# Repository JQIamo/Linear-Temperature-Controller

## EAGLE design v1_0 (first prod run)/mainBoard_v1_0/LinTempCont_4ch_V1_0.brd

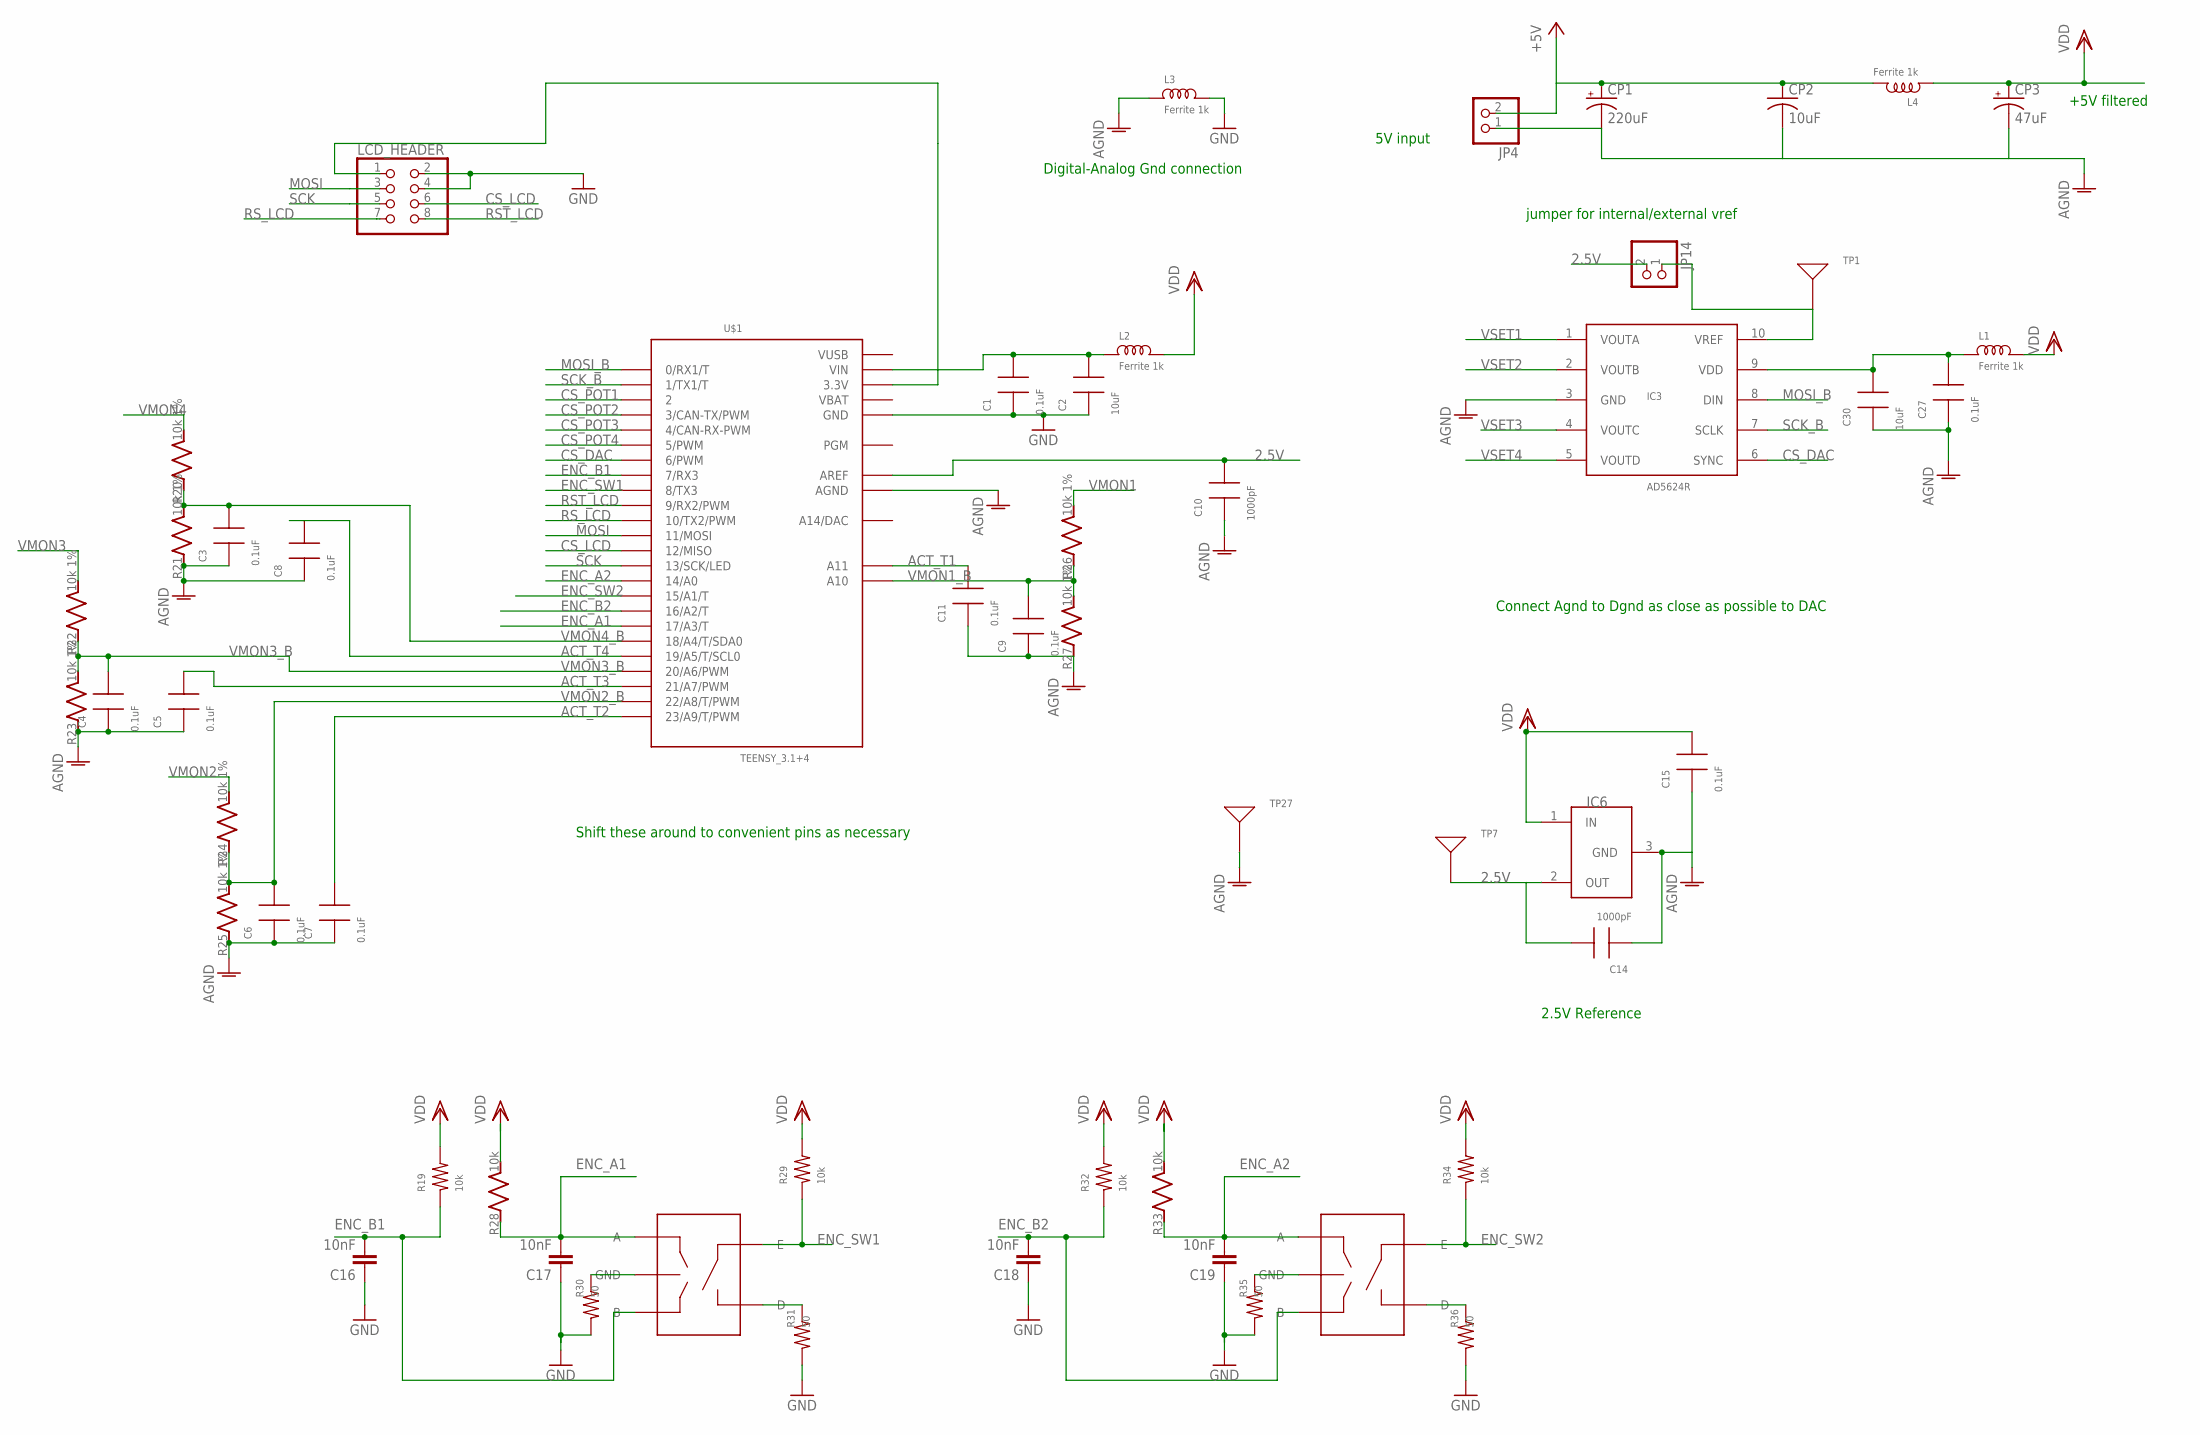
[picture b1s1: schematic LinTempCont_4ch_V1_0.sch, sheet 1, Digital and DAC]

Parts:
C1, C3, C4, C5, C6, C7, C8, C9, C11, C15, C27: 0.1uF; 0603
C2, C30: 10uF; 0805
C10, C14: 1000pF; 0603
C16, C17, C18, C19: 10nF; C0603
CP1: 220uF; PANASONIC_F
CP2: 10uF; C0805K
CP3: 47uF; CT7343
ENC1, ENC2: PEC09; PEC092320FS
IC3: AD5624R; MSOP10
IC6: TS6001; SOT-23
JP4: SCRWTRM-1X2; 1X02_SCRWTRM
JP14: PINHD-1X2; 1X02
L1, L2, L3, L4: Ferrite 1k; 0805
LCD_HEADER: PINHD-2X4-SHROUD; ML08
R19, R29, R32, R34: 10k; 0603
R20, R21, R22, R23, R24, R25, R26, R27: 10k 1%; R_0603
R28, R33: 10k; R_0603
R30, R31, R35, R36: 50; 0603
TP1, TP7, TP27: TESTPT; 1206TESTPAD
U$1: TEENSY_3.1+4

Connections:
2.5V: C10.2, C14.2, IC6.2 (OUT), JP14.2, TP7.P$1, U$1.AREF; also elsewhere on the board
3.3V: LCD_HEADER.1, U$1.3.3V, U$1.3.3V1 (3.3V)
+5V: CP1.+, CP2.1, JP4.2, L4.2
ACT_T1: C11.2, U$1.A11; also elsewhere on the board
ACT_T2: C7.2, U$1.23/A9 (23/A9/T/PWM); also elsewhere on the board
ACT_T3: C5.2, U$1.21/A7 (21/A7/PWM); also elsewhere on the board
ACT_T4: C8.2, U$1.19/A5 (19/A5/T/SCL0); also elsewhere on the board
AGND: C3.1, C4.1, C5.1, C6.1, C7.1, C8.1, C9.1, C10.1, C11.1, C14.1, C15.1, C27.1, C30.1, CP1.-, CP2.2, CP3.-, IC3.3 (GND), IC6.3 (GND), JP4.1, L3.1, R21.P$1 (1), R23.P$1 (1), R25.P$1 (1), R27.P$1 (1), TP27.P$1, U$1.AGND; also elsewhere on the board
CS_DAC: IC3.6 (SYNC), U$1.6 (6/PWM)
CS_LCD: LCD_HEADER.6, U$1.12 (12/MISO)
CS_POT1: U$1.2; also elsewhere on the board
CS_POT2: U$1.3 (3/CAN-TX/PWM); also elsewhere on the board
CS_POT3: U$1.4 (4/CAN-RX-PWM); also elsewhere on the board
CS_POT4: U$1.5 (5/PWM); also elsewhere on the board
DGND: C1.1, C2.1, C16.1, C17.1, C18.1, C19.1, L3.2, LCD_HEADER.2, LCD_HEADER.4, R30.1, R31.1, R35.1, R36.1, U$1.GND, U$1.GND1 (GND); also elsewhere on the board
ENC_A1: C17.2, ENC1.A, R28.P$1 (1), U$1.17/A3 (17/A3/T)
ENC_A2: C19.2, ENC2.A, R33.P$1 (1), U$1.14/A0
ENC_B1: C16.2, ENC1.B, R19.1, U$1.7 (7/RX3)
ENC_B2: C18.2, ENC2.B, R32.1, U$1.16/A2 (16/A2/T)
ENC_SW1: ENC1.E, R29.1, U$1.8 (8/TX3)
ENC_SW2: ENC2.E, R34.1, U$1.15/A1 (15/A1/T)
MOSI: LCD_HEADER.3, U$1.11 (11/MOSI)
MOSI_B: IC3.8 (DIN), U$1.0 (0/RX1/T); also elsewhere on the board
unnamed: IC3.10 (VREF), JP14.1, TP1.P$1
unnamed: ENC1.C (GND), R30.2
unnamed: ENC1.D, R31.2
unnamed: ENC2.C (GND), R35.2
unnamed: ENC2.D, R36.2
unnamed: C27.2, C30.2, IC3.9 (VDD), L1.1
unnamed: C1.2, C2.2, L2.1, U$1.VIN
RST_LCD: LCD_HEADER.8, U$1.9 (9/RX2/PWM)
RS_LCD: LCD_HEADER.7, U$1.10 (10/TX2/PWM)
SCK: LCD_HEADER.5, U$1.13 (13/SCK/LED)
SCK_B: IC3.7 (SCLK), U$1.1 (1/TX1/T); also elsewhere on the board
VBAT: U$1.VBAT
VDD: C15.2, CP3.+, IC6.1 (IN), L1.2, L2.2, L4.1, R19.2, R28.P$2 (2), R29.2, R32.2, R33.P$2 (2), R34.2; also elsewhere on the board
VMON1: R26.P$2 (2); also elsewhere on the board
VMON1_B: C9.2, R26.P$1 (1), R27.P$2 (2), U$1.A10
VMON2: R24.P$2 (2); also elsewhere on the board
VMON2_B: C6.2, R24.P$1 (1), R25.P$2 (2), U$1.22/A8 (22/A8/T/PWM)
VMON3: R22.P$2 (2); also elsewhere on the board
VMON3_B: C4.2, R22.P$1 (1), R23.P$2 (2), U$1.20/A6 (20/A6/PWM)
VMON4: R20.P$2 (2); also elsewhere on the board
VMON4_B: C3.2, R20.P$1 (1), R21.P$2 (2), U$1.18/A4 (18/A4/T/SDA0)
VSET1: IC3.1 (VOUTA); also elsewhere on the board
VSET2: IC3.2 (VOUTB); also elsewhere on the board
VSET3: IC3.4 (VOUTC); also elsewhere on the board
VSET4: IC3.5 (VOUTD); also elsewhere on the board
VUSB: U$1.VUSB

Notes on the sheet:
Shift these around to convenient pins as necessary
Digital-Analog Gnd connection
Connect Agnd to Dgnd as close as possible to DAC
2.5V Reference
+5V filtered
5V input
jumper for internal/external vref

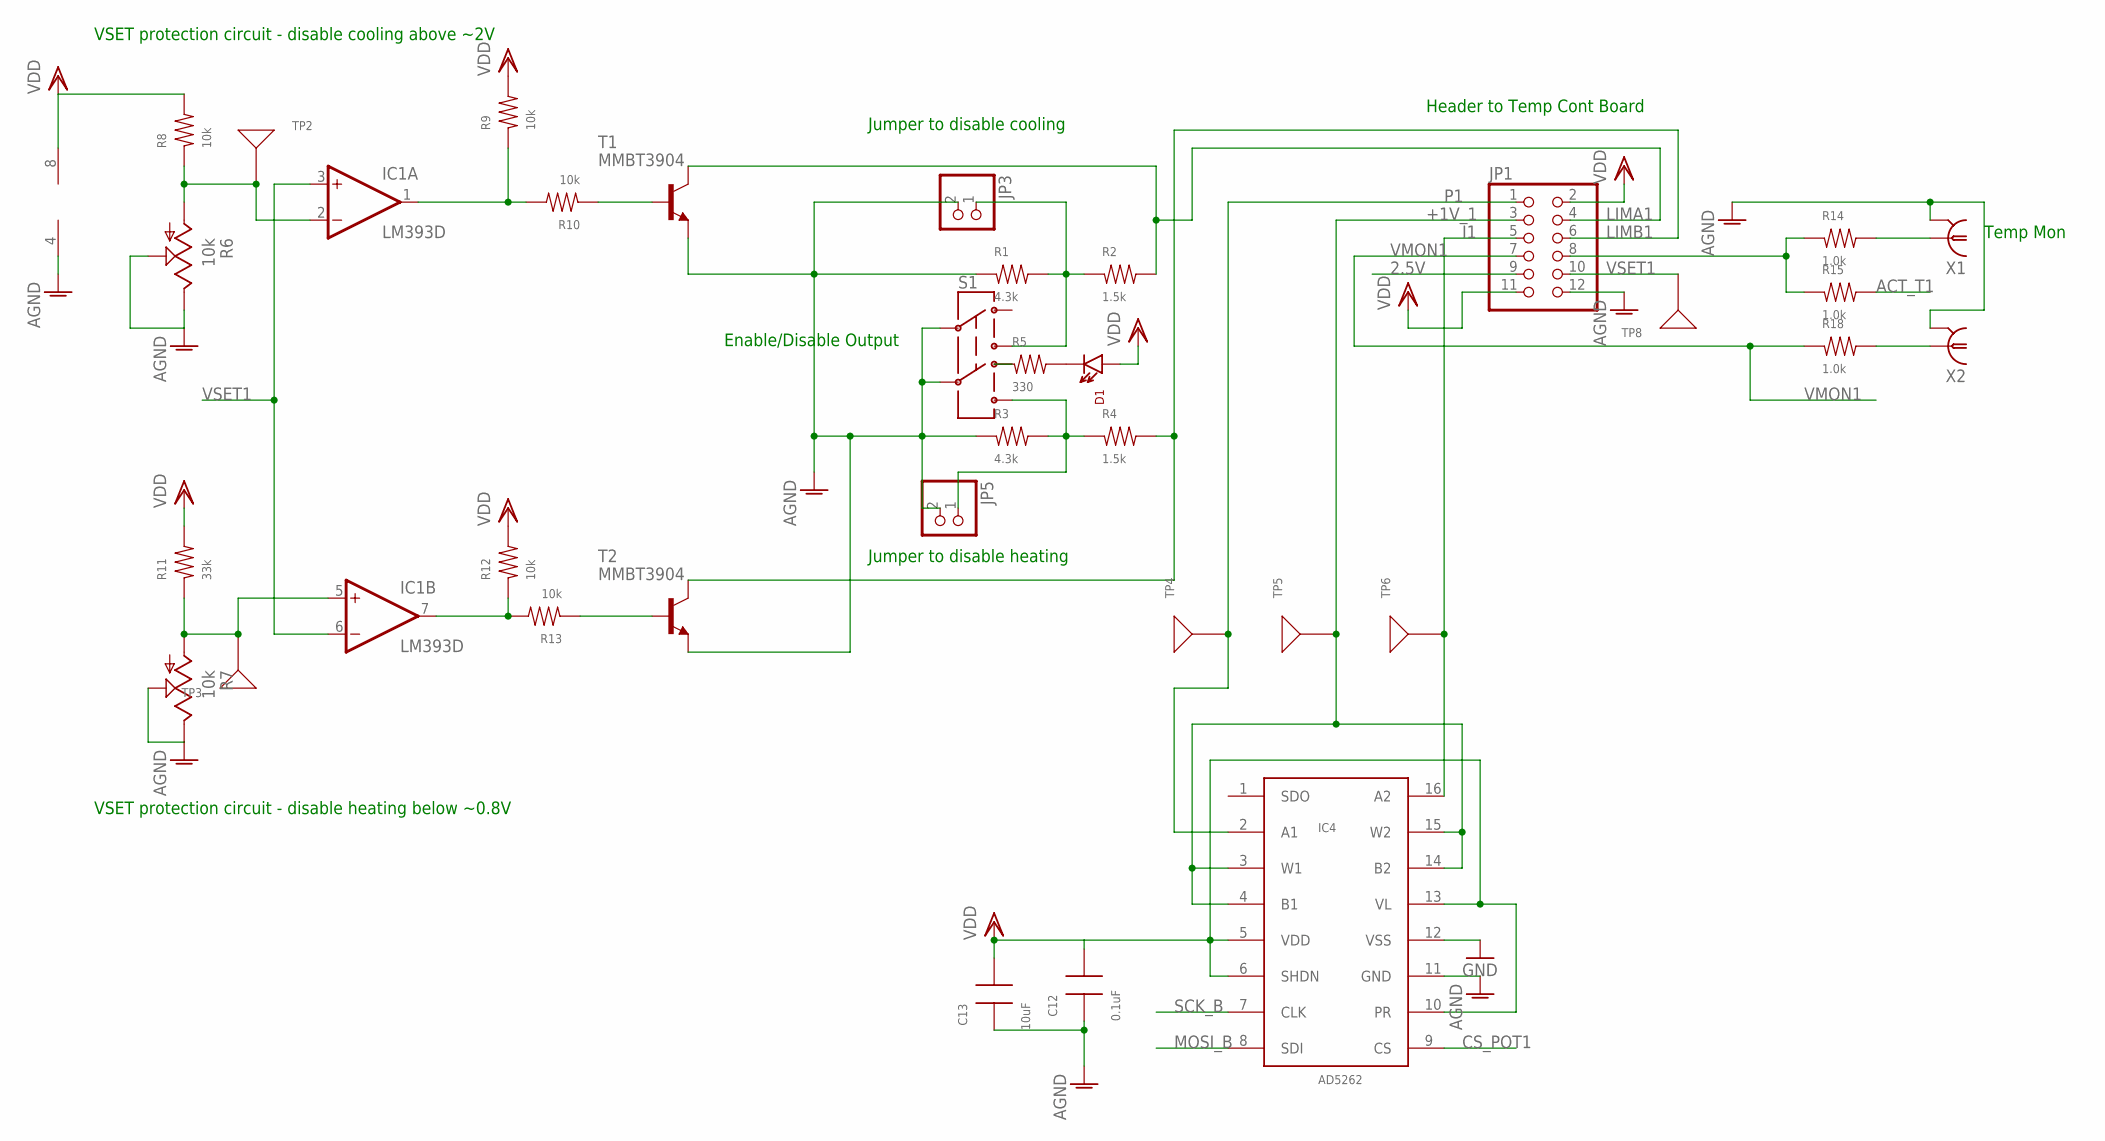
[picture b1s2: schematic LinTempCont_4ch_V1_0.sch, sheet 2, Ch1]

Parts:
C12: 0.1uF; 0603
C13: 10uF; 0805
D1: LED/MINI-IND; HLMP--F0010
IC1: LM393D; SO08
IC4: AD5262; TSSOP16
JP1: PINHD-2X6/90; 2X06/90
JP3, JP5: PINHD-1X2; 1X02
R1, R3: 4.3k; 0603
R2, R4: 1.5k; 0603
R5: 330; 0603
R6, R7: 10k; 64WPOT
R8, R9, R10, R12, R13: 10k; 0603
R11: 33k; 0603
R14, R15, R18: 1.0k; 0603
S1: SWITCH-DPDT/VER; E-SWITCH-100-M7
T1, T2: MMBT3904; SOT-23
TP2, TP3, TP4, TP5, TP6, TP8: TESTPT; 1206TESTPAD
X1, X2: BNC-H; BNC90

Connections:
2.5V: JP1.9; also elsewhere on the board
+1V_1: IC4.3 (W1), IC4.4 (B1), IC4.14 (B2), IC4.15 (W2), JP1.3, TP5.P$1
ACT_T1: R15.2; also elsewhere on the board
AGND: C12.1, C13.1, IC1.4 (V-), IC4.11 (GND), JP1.12, JP3.2, JP5.2, R1.1, R3.1, R6.P$2 (2), R6.P$3 (3), R7.P$2 (2), R7.P$3 (3), S1.P$2 (2), S1.P$5 (5), T1.2 (E), T2.2 (E), X1.2, X2.2; also elsewhere on the board
CS_POT1: IC4.9 (CS); also elsewhere on the board
DGND: IC4.12 (VSS); also elsewhere on the board
I1: IC4.16 (A2), JP1.5, TP6.P$1
LIMA1: JP1.4, R2.2, T1.3 (C)
LIMB1: JP1.6, R4.2, T2.3 (C)
MOSI_B: IC4.8 (SDI); also elsewhere on the board
unnamed: JP3.1, R1.2, R2.1, S1.P$3 (3)
unnamed: R14.2, X1.1
unnamed: JP5.1, R3.2, R4.1, S1.P$6 (6)
unnamed: IC1.2 (-IN), R6.P$1 (1), R8.1, TP2.P$1
unnamed: IC1.5 (+IN), R7.P$1 (1), R11.1, TP3.P$1
unnamed: IC1.7 (OUT), R12.1, R13.2
unnamed: IC1.1 (OUT), R9.1, R10.2
unnamed: R10.1, T1.1 (B)
unnamed: R13.1, T2.1 (B)
unnamed: D1.C, R5.2
unnamed: R5.1, S1.P$4 (4)
unnamed: R18.2, X2.1
unnamed: JP1.8, R14.1, R15.1
P1: IC4.2 (A1), JP1.1, TP4.P$1
SCK_B: IC4.7 (CLK); also elsewhere on the board
VDD: C12.2, C13.2, D1.A, IC1.8 (V+), IC4.5 (VDD), IC4.6 (SHDN), IC4.10 (PR), IC4.13 (VL), JP1.2, JP1.11, R8.2, R9.2, R11.2, R12.2; also elsewhere on the board
VMON1: JP1.7, R18.1; also elsewhere on the board
VSET1: IC1.3 (+IN), IC1.6 (-IN), JP1.10, TP8.P$1; also elsewhere on the board

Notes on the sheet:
Header to Temp Cont Board
Jumper to disable heating
Jumper to disable cooling
Enable/Disable Output
VSET protection circuit - disable heating below ~0.8V
VSET protection circuit - disable cooling above ~2V
Temp Mon

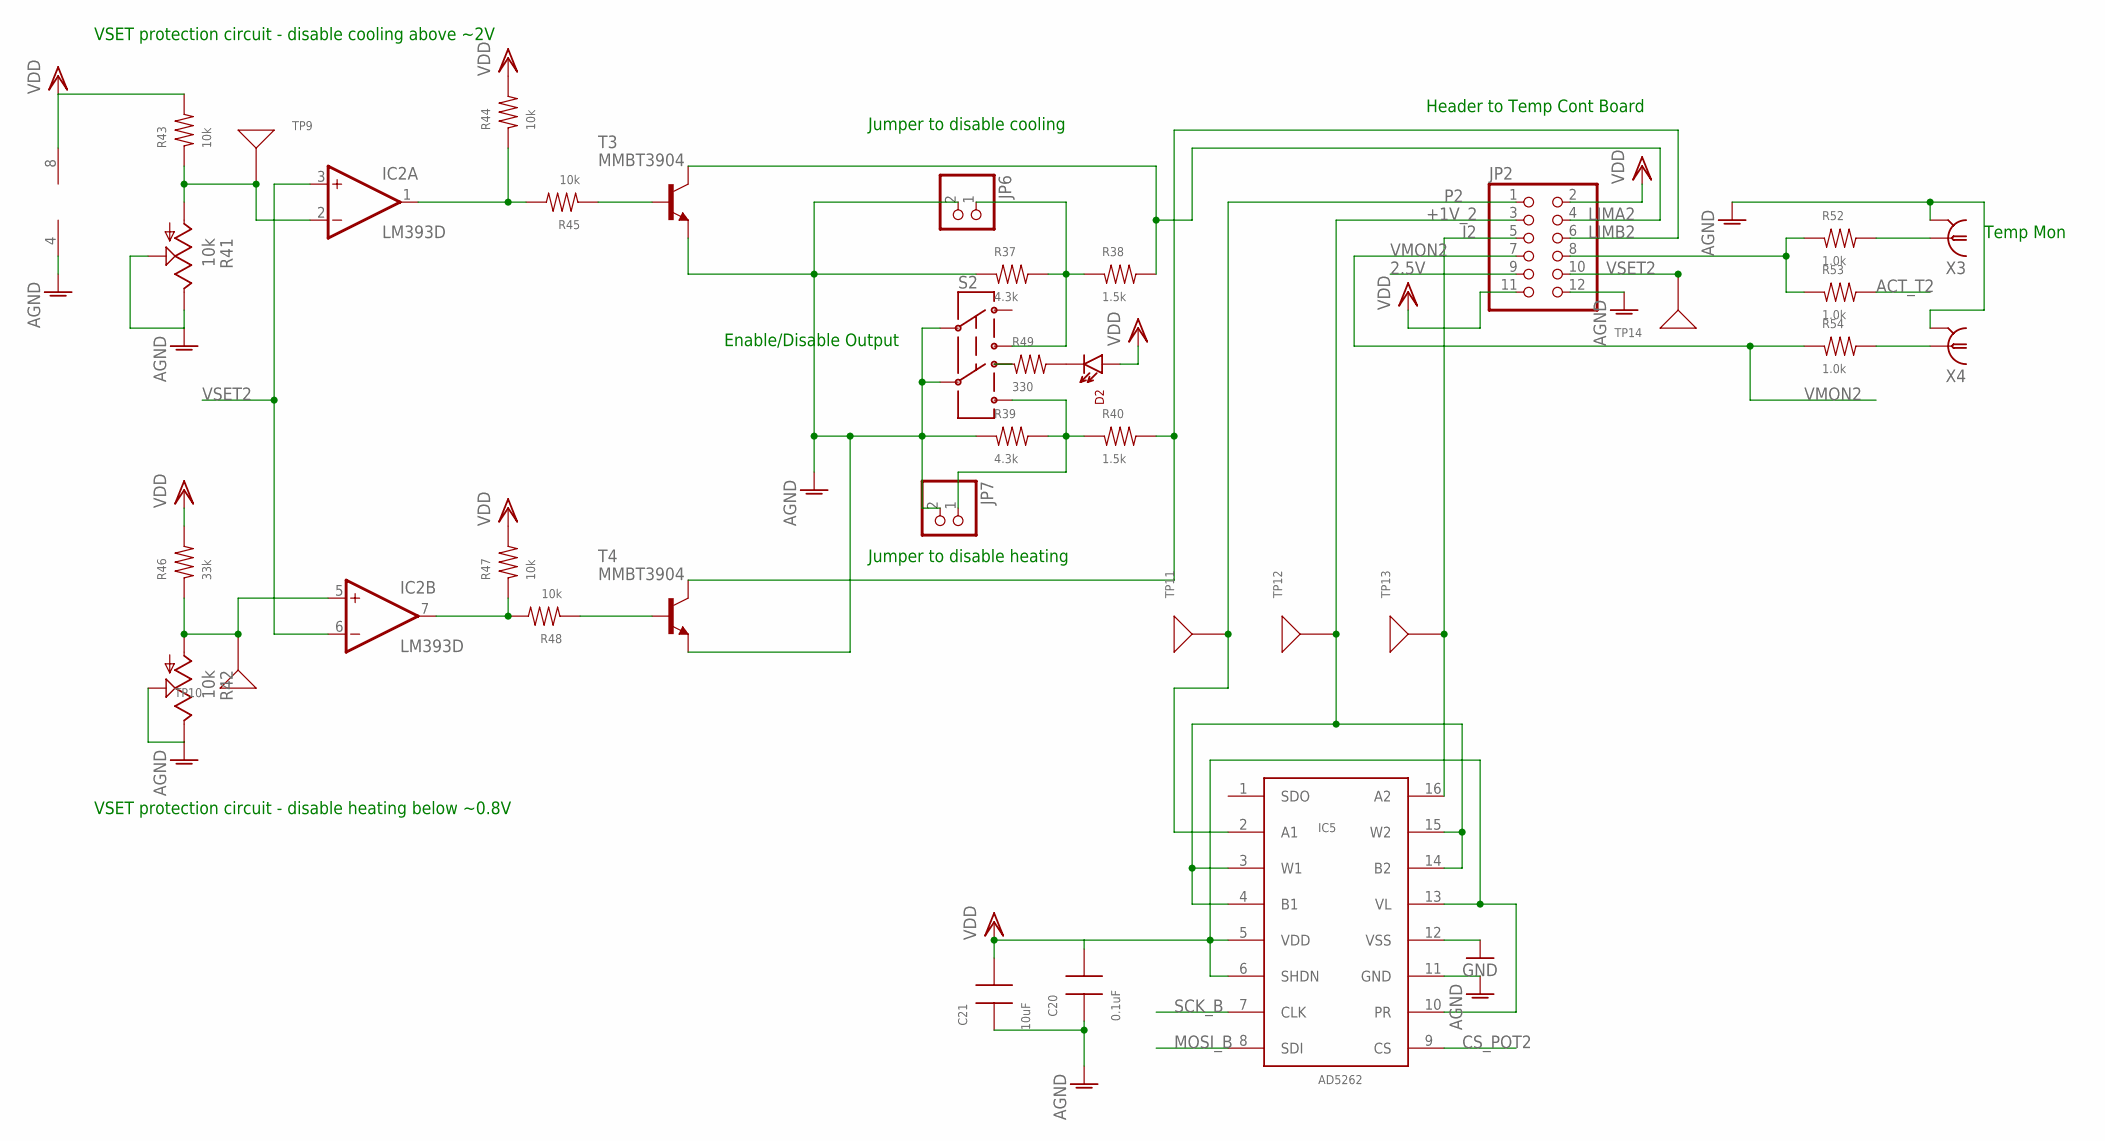
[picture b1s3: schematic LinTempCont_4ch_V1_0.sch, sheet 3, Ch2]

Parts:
C20: 0.1uF; 0603
C21: 10uF; 0805
D2: LED/MINI-IND; HLMP--F0010
IC2: LM393D; SO08
IC5: AD5262; TSSOP16
JP2: PINHD-2X6/90; 2X06/90
JP6, JP7: PINHD-1X2; 1X02
R37, R39: 4.3k; 0603
R38, R40: 1.5k; 0603
R41, R42: 10k; 64WPOT
R43, R44, R45, R47, R48: 10k; 0603
R46: 33k; 0603
R49: 330; 0603
R52, R53, R54: 1.0k; 0603
S2: SWITCH-DPDT/VER; E-SWITCH-100-M7
T3, T4: MMBT3904; SOT-23
TP9, TP10, TP11, TP12, TP13, TP14: TESTPT; 1206TESTPAD
X3, X4: BNC-H; BNC90

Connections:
2.5V: JP2.9; also elsewhere on the board
+1V_2: IC5.3 (W1), IC5.4 (B1), IC5.14 (B2), IC5.15 (W2), JP2.3, TP12.P$1
ACT_T2: R53.2; also elsewhere on the board
AGND: C20.1, C21.1, IC2.4 (V-), IC5.11 (GND), JP2.12, JP6.2, JP7.2, R37.1, R39.1, R41.P$2 (2), R41.P$3 (3), R42.P$2 (2), R42.P$3 (3), S2.P$2 (2), S2.P$5 (5), T3.2 (E), T4.2 (E), X3.2, X4.2; also elsewhere on the board
CS_POT2: IC5.9 (CS); also elsewhere on the board
DGND: IC5.12 (VSS); also elsewhere on the board
I2: IC5.16 (A2), JP2.5, TP13.P$1
LIMA2: JP2.4, R38.2, T3.3 (C)
LIMB2: JP2.6, R40.2, T4.3 (C)
MOSI_B: IC5.8 (SDI); also elsewhere on the board
unnamed: JP6.1, R37.2, R38.1, S2.P$3 (3)
unnamed: JP7.1, R39.2, R40.1, S2.P$6 (6)
unnamed: IC2.2 (-IN), R41.P$1 (1), R43.1, TP9.P$1
unnamed: IC2.1 (OUT), R44.1, R45.2
unnamed: R45.1, T3.1 (B)
unnamed: IC2.5 (+IN), R42.P$1 (1), R46.1, TP10.P$1
unnamed: IC2.7 (OUT), R47.1, R48.2
unnamed: R48.1, T4.1 (B)
unnamed: D2.C, R49.2
unnamed: R49.1, S2.P$4 (4)
unnamed: JP2.8, R52.1, R53.1
unnamed: R52.2, X3.1
unnamed: R54.2, X4.1
P2: IC5.2 (A1), JP2.1, TP11.P$1
SCK_B: IC5.7 (CLK); also elsewhere on the board
VDD: C20.2, C21.2, D2.A, IC2.8 (V+), IC5.5 (VDD), IC5.6 (SHDN), IC5.10 (PR), IC5.13 (VL), JP2.2, JP2.11, R43.2, R44.2, R46.2, R47.2; also elsewhere on the board
VMON2: JP2.7, R54.1; also elsewhere on the board
VSET2: IC2.3 (+IN), IC2.6 (-IN), JP2.10, TP14.P$1; also elsewhere on the board

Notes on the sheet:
Header to Temp Cont Board
Jumper to disable heating
Jumper to disable cooling
Enable/Disable Output
VSET protection circuit - disable heating below ~0.8V
VSET protection circuit - disable cooling above ~2V
Temp Mon

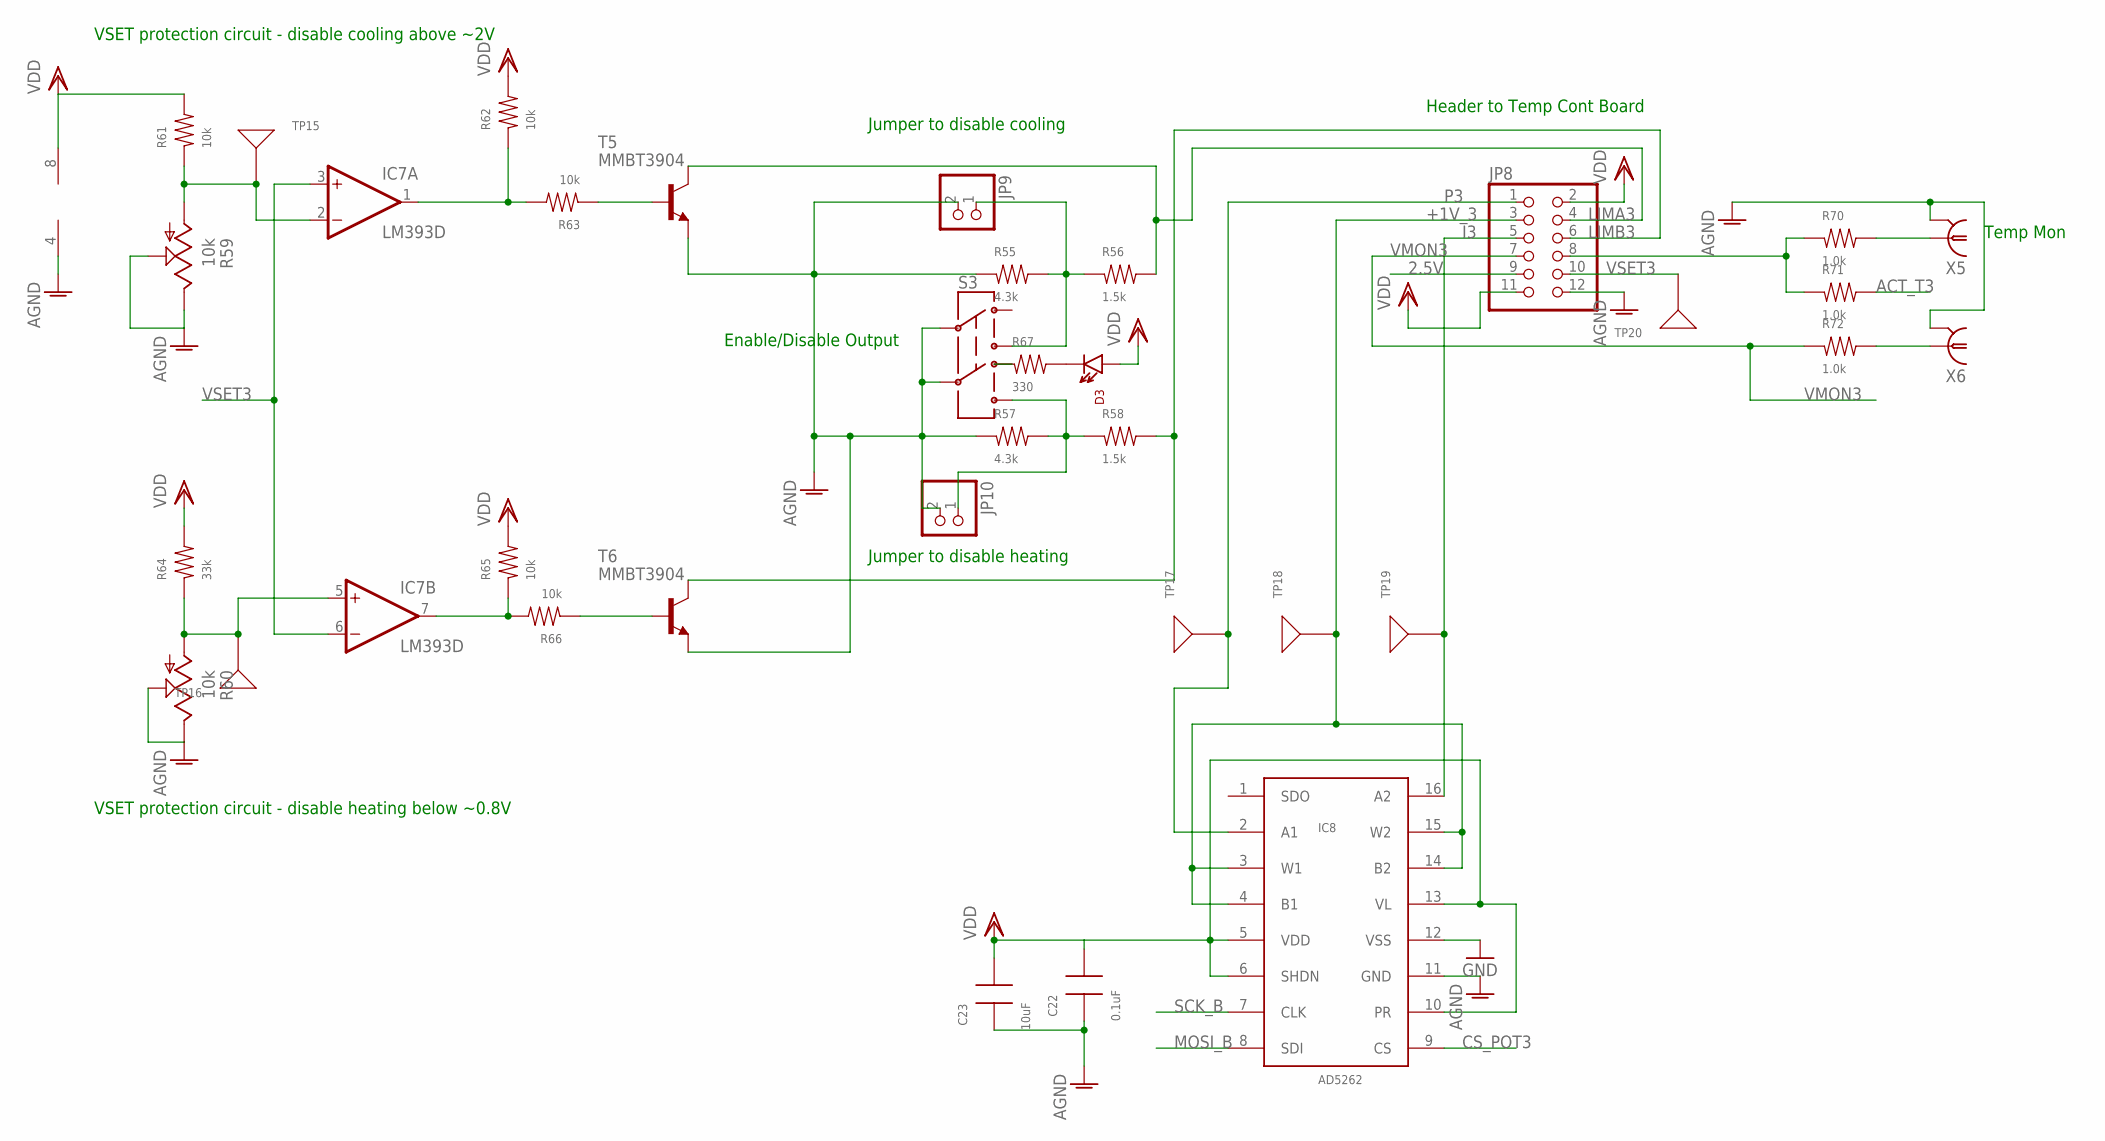
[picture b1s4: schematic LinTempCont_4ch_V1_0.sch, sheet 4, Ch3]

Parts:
C22: 0.1uF; 0603
C23: 10uF; 0805
D3: LED/MINI-IND; HLMP--F0010
IC7: LM393D; SO08
IC8: AD5262; TSSOP16
JP8: PINHD-2X6/90; 2X06/90
JP9, JP10: PINHD-1X2; 1X02
R55, R57: 4.3k; 0603
R56, R58: 1.5k; 0603
R59, R60: 10k; 64WPOT
R61, R62, R63, R65, R66: 10k; 0603
R64: 33k; 0603
R67: 330; 0603
R70, R71, R72: 1.0k; 0603
S3: SWITCH-DPDT/VER; E-SWITCH-100-M7
T5, T6: MMBT3904; SOT-23
TP15, TP16, TP17, TP18, TP19, TP20: TESTPT; 1206TESTPAD
X5, X6: BNC-H; BNC90

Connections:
2.5V: JP8.9; also elsewhere on the board
+1V_3: IC8.3 (W1), IC8.4 (B1), IC8.14 (B2), IC8.15 (W2), JP8.3, TP18.P$1
ACT_T3: R71.2; also elsewhere on the board
AGND: C22.1, C23.1, IC7.4 (V-), IC8.11 (GND), JP8.12, JP9.2, JP10.2, R55.1, R57.1, R59.P$2 (2), R59.P$3 (3), R60.P$2 (2), R60.P$3 (3), S3.P$2 (2), S3.P$5 (5), T5.2 (E), T6.2 (E), X5.2, X6.2; also elsewhere on the board
CS_POT3: IC8.9 (CS); also elsewhere on the board
DGND: IC8.12 (VSS); also elsewhere on the board
I3: IC8.16 (A2), JP8.5, TP19.P$1
LIMA3: JP8.4, R56.2, T5.3 (C)
LIMB3: JP8.6, R58.2, T6.3 (C)
MOSI_B: IC8.8 (SDI); also elsewhere on the board
unnamed: JP9.1, R55.2, R56.1, S3.P$3 (3)
unnamed: JP10.1, R57.2, R58.1, S3.P$6 (6)
unnamed: IC7.2 (-IN), R59.P$1 (1), R61.1, TP15.P$1
unnamed: IC7.1 (OUT), R62.1, R63.2
unnamed: R63.1, T5.1 (B)
unnamed: IC7.5 (+IN), R60.P$1 (1), R64.1, TP16.P$1
unnamed: IC7.7 (OUT), R65.1, R66.2
unnamed: R66.1, T6.1 (B)
unnamed: D3.C, R67.2
unnamed: R67.1, S3.P$4 (4)
unnamed: JP8.8, R70.1, R71.1
unnamed: R70.2, X5.1
unnamed: R72.2, X6.1
P3: IC8.2 (A1), JP8.1, TP17.P$1
SCK_B: IC8.7 (CLK); also elsewhere on the board
VDD: C22.2, C23.2, D3.A, IC7.8 (V+), IC8.5 (VDD), IC8.6 (SHDN), IC8.10 (PR), IC8.13 (VL), JP8.2, JP8.11, R61.2, R62.2, R64.2, R65.2; also elsewhere on the board
VMON3: JP8.7, R72.1; also elsewhere on the board
VSET3: IC7.3 (+IN), IC7.6 (-IN), JP8.10, TP20.P$1; also elsewhere on the board

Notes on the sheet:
Header to Temp Cont Board
Jumper to disable heating
Jumper to disable cooling
Enable/Disable Output
VSET protection circuit - disable heating below ~0.8V
VSET protection circuit - disable cooling above ~2V
Temp Mon

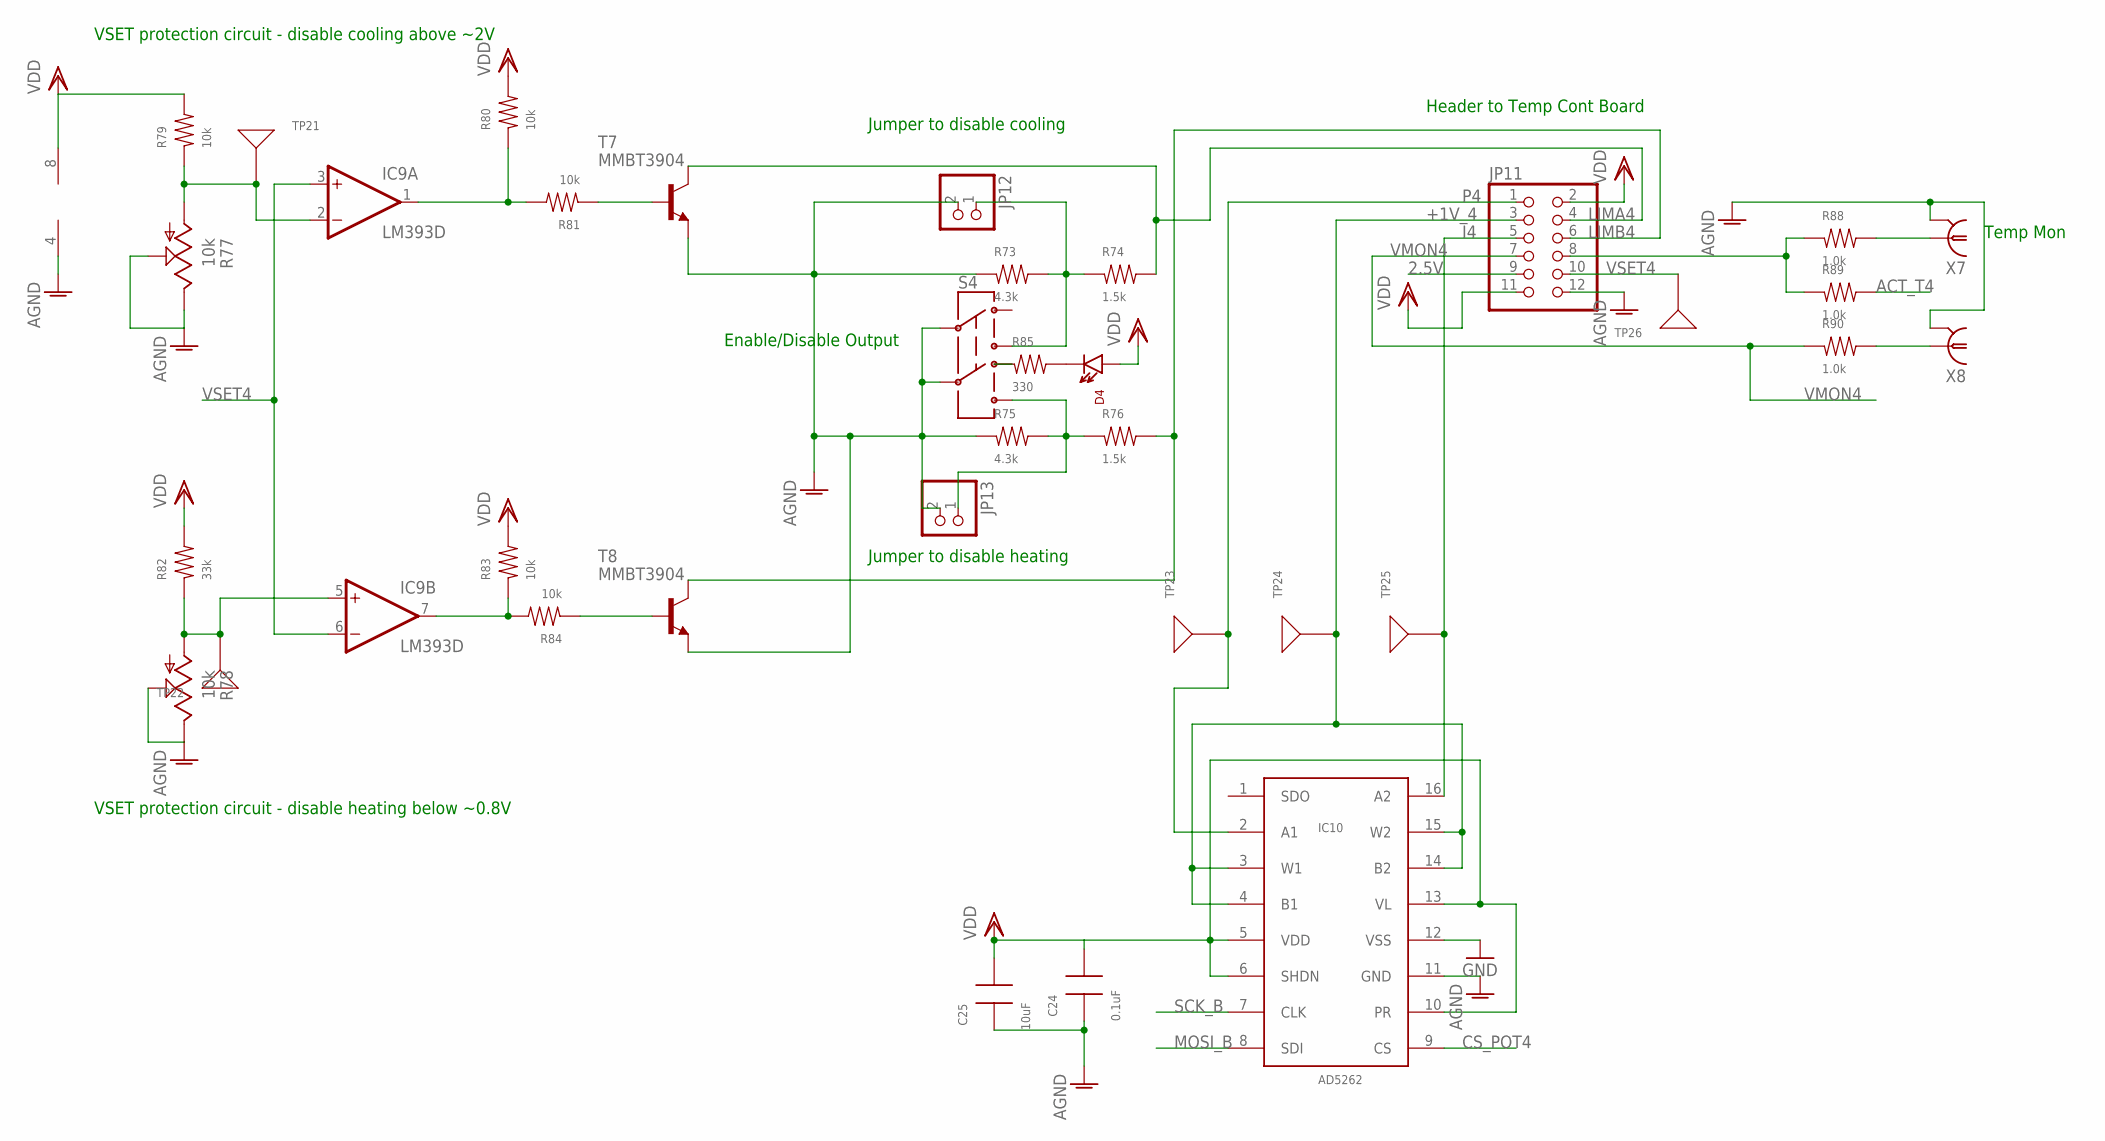
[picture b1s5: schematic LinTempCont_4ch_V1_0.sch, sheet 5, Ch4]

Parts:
C24: 0.1uF; 0603
C25: 10uF; 0805
D4: LED/MINI-IND; HLMP--F0010
IC9: LM393D; SO08
IC10: AD5262; TSSOP16
JP11: PINHD-2X6/90; 2X06/90
JP12, JP13: PINHD-1X2; 1X02
R73, R75: 4.3k; 0603
R74, R76: 1.5k; 0603
R77, R78: 10k; 64WPOT
R79, R80, R81, R83, R84: 10k; 0603
R82: 33k; 0603
R85: 330; 0603
R88, R89, R90: 1.0k; 0603
S4: SWITCH-DPDT/VER; E-SWITCH-100-M7
T7, T8: MMBT3904; SOT-23
TP21, TP22, TP23, TP24, TP25, TP26: TESTPT; 1206TESTPAD
X7, X8: BNC-H; BNC90

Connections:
2.5V: JP11.9; also elsewhere on the board
+1V_4: IC10.3 (W1), IC10.4 (B1), IC10.14 (B2), IC10.15 (W2), JP11.3, TP24.P$1
ACT_T4: R89.2; also elsewhere on the board
AGND: C24.1, C25.1, IC9.4 (V-), IC10.11 (GND), JP11.12, JP12.2, JP13.2, R73.1, R75.1, R77.P$2 (2), R77.P$3 (3), R78.P$2 (2), R78.P$3 (3), S4.P$2 (2), S4.P$5 (5), T7.2 (E), T8.2 (E), X7.2, X8.2; also elsewhere on the board
CS_POT4: IC10.9 (CS); also elsewhere on the board
DGND: IC10.12 (VSS); also elsewhere on the board
I4: IC10.16 (A2), JP11.5, TP25.P$1
LIMA4: JP11.4, R74.2, T7.3 (C)
LIMB4: JP11.6, R76.2, T8.3 (C)
MOSI_B: IC10.8 (SDI); also elsewhere on the board
unnamed: JP12.1, R73.2, R74.1, S4.P$3 (3)
unnamed: JP13.1, R75.2, R76.1, S4.P$6 (6)
unnamed: IC9.2 (-IN), R77.P$1 (1), R79.1, TP21.P$1
unnamed: IC9.1 (OUT), R80.1, R81.2
unnamed: R81.1, T7.1 (B)
unnamed: IC9.5 (+IN), R78.P$1 (1), R82.1, TP22.P$1
unnamed: IC9.7 (OUT), R83.1, R84.2
unnamed: R84.1, T8.1 (B)
unnamed: D4.C, R85.2
unnamed: R85.1, S4.P$4 (4)
unnamed: JP11.8, R88.1, R89.1
unnamed: R88.2, X7.1
unnamed: R90.2, X8.1
P4: IC10.2 (A1), JP11.1, TP23.P$1
SCK_B: IC10.7 (CLK); also elsewhere on the board
VDD: C24.2, C25.2, D4.A, IC9.8 (V+), IC10.5 (VDD), IC10.6 (SHDN), IC10.10 (PR), IC10.13 (VL), JP11.2, JP11.11, R79.2, R80.2, R82.2, R83.2; also elsewhere on the board
VMON4: JP11.7, R90.1; also elsewhere on the board
VSET4: IC9.3 (+IN), IC9.6 (-IN), JP11.10, TP26.P$1; also elsewhere on the board

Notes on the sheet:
Header to Temp Cont Board
Jumper to disable heating
Jumper to disable cooling
Enable/Disable Output
VSET protection circuit - disable heating below ~0.8V
VSET protection circuit - disable cooling above ~2V
Temp Mon

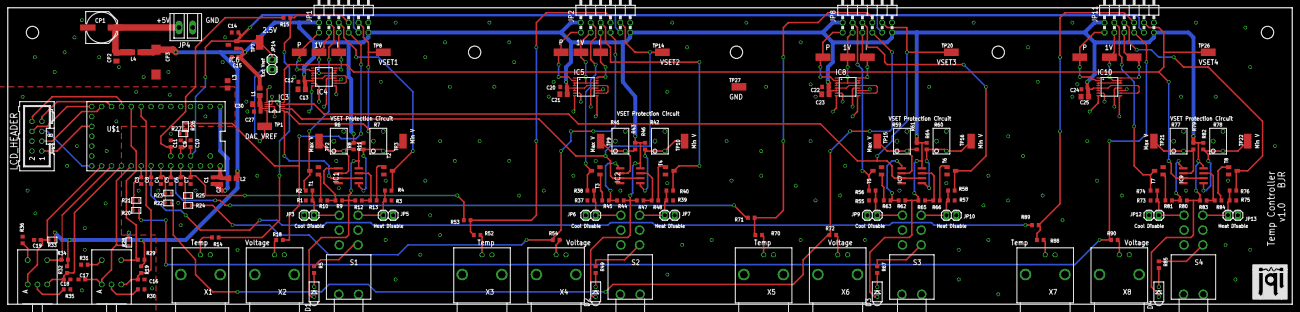
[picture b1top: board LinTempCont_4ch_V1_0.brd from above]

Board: 4 copper layers, 330.2 x 76.2 mm, 196 parts (0 on the bottom side), 119 nets.

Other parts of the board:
U$2: JQI_LOGO_NEGATIVE-SILKSCREEN

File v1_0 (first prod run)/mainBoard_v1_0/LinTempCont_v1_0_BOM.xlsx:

Item # | Qty | Value | Ref Des | Device | Package | Description | DIGIKEY | Type | Comments
1 | 4 |  | D1, D2, D3, D4 | LED/MINI-IND | HLMP--F0010 | Through-hole, side-view LED | 516-1417-ND | thru-hole
2 | 9 |  | JP3, JP5, JP6, JP7, JP9, JP10, JP12, JP13, JP14 | PINHD-1X2 | 1X02 | PIN HEADER | 952-2262-ND | thru-hole
3 | 1 |  | LCD_HEADER | PINHD-2X4-SHROUD | ML08 | PIN HEADER | 609-3530-ND | thru-hole
4 | 4 |  | JP1, JP2, JP8, JP11 | PINHD-2X6/90 | 2X06/90 | PIN HEADER | 609-3345-ND | thru-hole
5 | 1 |  | JP4 | SCRWTRM-1X2 | 1X02_SCRWTRM | Screw Terminal | ED2635-ND | thru-hole
6 | 4 |  | S1, S2, S3, S4 | SWITCH-DPDT/VER | E-SWITCH-100-M7 | DPDT Switch | 100DP1T2B4M7QE-ND | thru-hole
7 | 1 |  | IC6 | TS6001 | SOT-23 | 2.5V Reference IC | TS6001BIG325TCT-ND | smt
8 | 15 | 0.1uF | C1, C3, C4, C5, C6, C7, C8, C9, C11, C12, C15, C20, C22, C24, C27 | CAP0603 | 0603 | SMT Capacitor | 399-5089-1-ND | smt
9 | 12 | 1.0k | R14, R15, R18, R52, R53, R54, R70, R71, R72, R88, R89, R90 | RES0603 | 0603 | SMT Resistor | MCT0603-1.00K-CFCT-ND | smt
10 | 8 | 1.5k | R2, R4, R38, R40, R56, R58, R74, R76 | RES0603 | 0603 | SMT Resistor | MCT0603-1.50K-CFCT-ND | smt
11 | 2 | 1000pF | C10, C14 | CAP0603 | 0603 | SMT Capacitor | 399-3293-1-ND | smt
12 | 8 | 10k | R6, R7, R41, R42, R59, R60, R77, R78 | MODEL64_TRIMPOT/TOP-ADJ | 64WPOT | Trimpot | 987-1061-ND | thru-hole
13 | 34 | 10k | R8, R9, R10, R12, R13, R19, R20, R21, R22, R23, R24, R25, R26, R27, R28, R29, R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 | RES0603 | 0603 | SMT Resistor | MCT0603-10.0K-CFCT-ND | smt
14 | 4 | 10nF | C16, C17, C18, C19 | C-EUC0603 | C0603 | SMT Capacitor | 399-1091-1-ND | smt
15 | 7 | 10uF | CP2, C2, C13, C21, C23, C25, C30 | CAP0805 | 0805 | SMT Capacitor | 1276-2891-1-ND | smt
16 | 1 | 220uF | CP1 | CPOL-USF | PANASONIC_F | SMT Polarized Capacitor | PCE3955CT-ND | smt
17 | 4 | 330 | R5, R49, R67, R85 | RES0603 | 0603 | SMT Resistor | MCT0603-330-CFCT-ND | smt
18 | 4 | 33k | R11, R46, R64, R82 | RES0603 | 0603 | SMT Resistor | MCT0603-33.0K-CFCT-ND | smt
19 | 8 | 4.3k | R1, R3, R37, R39, R55, R57, R73, R75 | RES0603 | 0603 | SMT Resistor | 541-4.3KGCT-ND | smt
20 | 1 | 47uF | CP3 | CPOL-USCT7343 | CT7343 | SMT Polarized Capacitor | 495-1571-1-ND | smt
21 | 4 | 50 | R30, R31, R35, R36 | RES0603 | 0603 | SMT Resistor | 541-51GCT-ND | smt
22 | 4 | AD5262 | IC4, IC5, IC8, IC10 | AD5262 | TSSOP16 | AD5262 dual circuit digital pot | AD5262BRUZ200-ND | smt
23 | 1 | AD5624R | IC3 | AD5624R | MSOP10 | AD5624R Quad Output DAC w/internal Vref | AD5624RBRMZ-3-ND | smt
24 | 8 | BNC-H | X1, X2, X3, X4, X5, X6, X7, X8 | BNC-H | BNC90 | BNC Connector. | A32260-ND | thru-hole
25 | 4 | Ferrite 1k | L1, L2, L3, L4 | INDUCTOR-0805 | 0805 | SMT Inductor. | 445-5223-1-ND | smt
26 | 4 | LM393D | IC1, IC2, IC7, IC9 | LM393D | SO08 | COMPARATOR | 296-1015-5-ND | smt
27 | 8 | MMBT3904 | T1, T2, T3, T4, T5, T6, T7, T8 | MMBT3904 | SOT-23 | NPN TRANSISTOR | MMBT3904-FDICT-ND | smt
28 | 2 | PEC09 | ENC1, ENC2 | PEC09 | PEC092320FS | PEC09-2320F-S0015 Rotary Encoder (Bourns). | PEC09-2320F-S0015-ND | thru-hole
29 | 1 | TEENSY_3.1+4 | U$1 | TEENSY_3.1+4 | TEENSY_3.1+4 | Footprint for Teensy 3.1 board using all through-holes |  | DNP | **DO NOT PLACE
30 | 27 | TESTPT | TP1, TP2, TP3, TP4, TP5, TP6, TP7, TP8, TP9, TP10, TP11, TP12, TP13, TP14, TP15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 | TESTPT | 1206TESTPAD |  | A106143CT-ND | smt
